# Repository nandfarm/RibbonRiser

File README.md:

# RibbonRiser
Lenovo Tiny 5 series riser card with a ribbon extension to connect an extra NVME and preserve an x16 PCIe connector

"This project is sponsored by PCBWay. Whether for small projects or complex designs, PCBWay offers quality PCB manufacturing, PCBA services, and CNC machining with industry-leading customization options, competitive pricing, and high-quality, end-to-end service. Prototype PCB orders start at a minimum of 5 pieces, with prices as low as $5. Learn more at www.pcbway.com ."

This is a prototype version of the device intended to check the impedance traces and the ribbon design. DO NOT reproduce as it is not guaranteed to work yet.

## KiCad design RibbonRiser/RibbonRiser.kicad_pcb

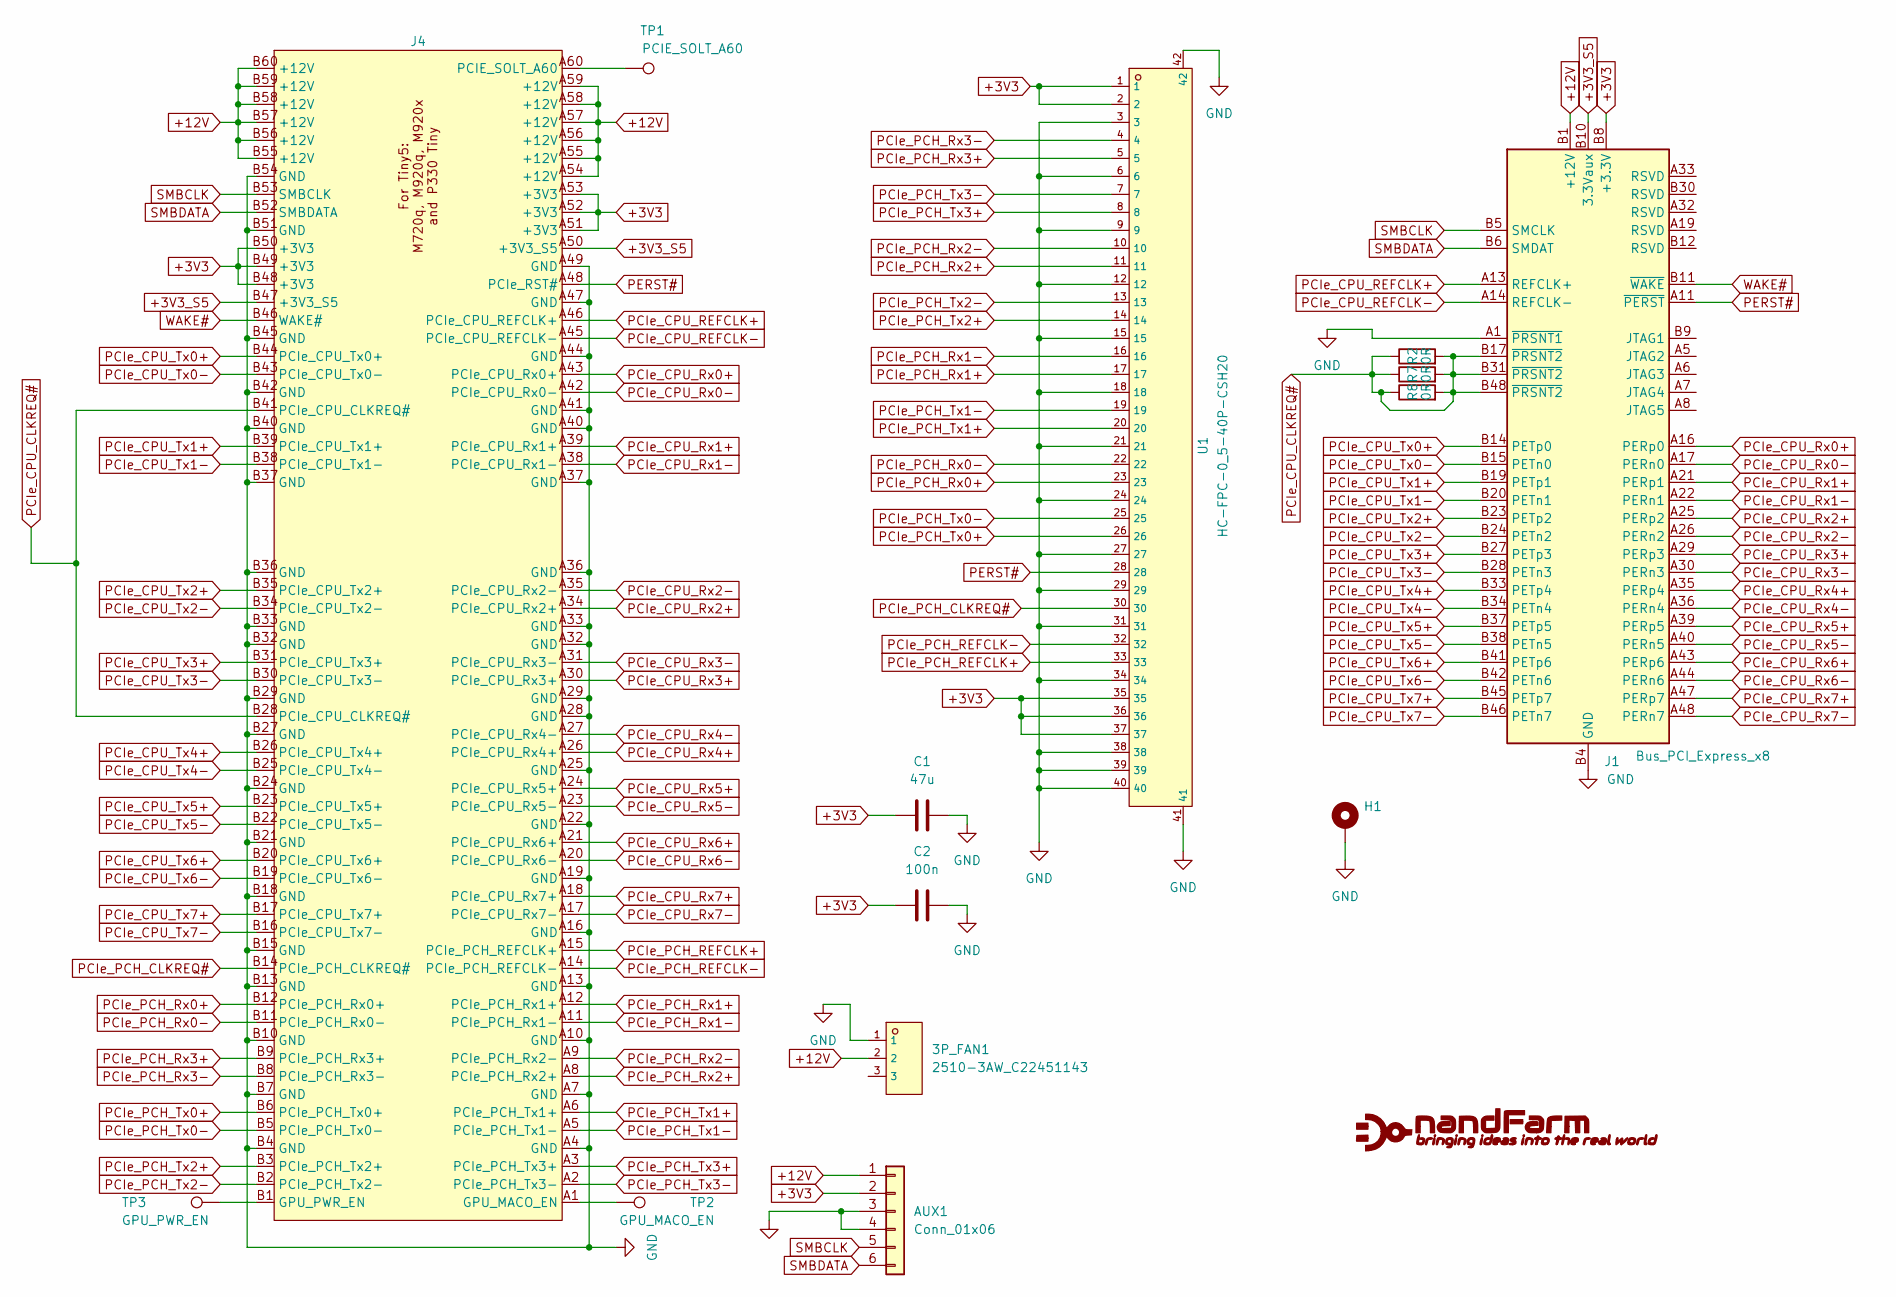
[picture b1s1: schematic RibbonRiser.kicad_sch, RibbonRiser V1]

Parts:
3P_FAN1: 2510-3AW_C22451143; CONN-TH_2510-3AW; LCSC C22451143
AUX1: Conn_01x06; PinHeader_1x06_P2.54mm_Vertical
C1: 47u; C_1206_3216Metric_Pad1.33x1.80mm_HandSolder
C2: 100n; C_0805_2012Metric_Pad1.18x1.45mm_HandSolder
H1: MountingHole_Pad; MountingHole_4.3mm_M4_ISO7380_Pad_TopOnly
J1: Bus_PCI_Express_x8; CONN-TH_98P-P1.00-V_3183-XXXXXPXT
J4: TinyRiser_connector
R2, R7, R8: 0R; R_0603_1608Metric_Pad0.98x0.95mm_HandSolder
TP1: PCIE_SOLT_A60; TestPoint_Pad_D1.0mm
TP2: GPU_MACO_EN; TestPoint_Pad_D1.0mm
TP3: GPU_PWR_EN; TestPoint_Pad_D1.0mm
U1: HC-FPC-0_5-40P-CSH20; FPC-SMD_40P-P0.50_HC-FPC-0.5-40P-CSH20; LCSC C19273956

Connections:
+3V3: AUX1.2, C1.1, C2.1, J1.A9 (+3.3V), J1.A10 (+3.3V), J1.B8 (+3.3V), J4.A51 (+3V3), J4.A52 (+3V3), J4.A53 (+3V3), J4.B48 (+3V3), J4.B49 (+3V3), J4.B50 (+3V3), U1.1, U1.2, U1.35, U1.36, U1.37
+3V3_S5: J1.B10 (3.3Vaux), J4.A50 (+3V3_S5), J4.B47 (+3V3_S5)
+12V: 3P_FAN1.2, AUX1.1, J1.A2 (+12V), J1.A3 (+12V), J1.B1 (+12V), J1.B2 (+12V), J1.B3 (+12V), J4.A54 (+12V), J4.A55 (+12V), J4.A56 (+12V), J4.A57 (+12V), J4.A58 (+12V), J4.A59 (+12V), J4.B55 (+12V), J4.B56 (+12V), J4.B57 (+12V), J4.B58 (+12V), J4.B59 (+12V), J4.B60 (+12V)
GND: 3P_FAN1.1, AUX1.3, AUX1.4, C1.2, C2.2, H1.1, J1.A1 (~PRSNT1), J1.A4 (GND), J1.A12 (GND), J1.A15 (GND), J1.A18 (GND), J1.A20 (GND), J1.A23 (GND), J1.A24 (GND), J1.A27 (GND), J1.A28 (GND), J1.A31 (GND), J1.A34 (GND), J1.A37 (GND), J1.A38 (GND), J1.A41 (GND), J1.A42 (GND), J1.A45 (GND), J1.A46 (GND), J1.A49 (GND), J1.B4 (GND), J1.B7 (GND), J1.B13 (GND), J1.B16 (GND), J1.B18 (GND), J1.B21 (GND), J1.B22 (GND), J1.B25 (GND), J1.B26 (GND), J1.B29 (GND), J1.B32 (GND), J1.B35 (GND), J1.B36 (GND), J1.B39 (GND), J1.B40 (GND), J1.B43 (GND), J1.B44 (GND), J1.B47 (GND), J1.B49 (GND), J4.A4 (GND), J4.A7 (GND), J4.A10 (GND), J4.A13 (GND), J4.A16 (GND), J4.A19 (GND), J4.A22 (GND), J4.A25 (GND), J4.A28 (GND), J4.A29 (GND), J4.A32 (GND), J4.A33 (GND), J4.A36 (GND), J4.A37 (GND), J4.A40 (GND), J4.A41 (GND), J4.A44 (GND), J4.A47 (GND), J4.A49 (GND), J4.B4 (GND), J4.B7 (GND), J4.B10 (GND), J4.B13 (GND), J4.B15 (GND), J4.B18 (GND), J4.B21 (GND), J4.B24 (GND), J4.B27 (GND), J4.B29 (GND), J4.B32 (GND), J4.B33 (GND), J4.B36 (GND), J4.B37 (GND), J4.B40 (GND), J4.B42 (GND), J4.B45 (GND), J4.B51 (GND), J4.B54 (GND), U1.3, U1.6, U1.9, U1.12, U1.15, U1.18, U1.21, U1.24, U1.27, U1.29, U1.31, U1.34, U1.38, U1.39, U1.40, U1.41, U1.42
unnamed: J4.A1 (GPU_MACO_EN), TP2.1
unnamed: J4.B1 (GPU_PWR_EN), TP3.1
unnamed: J4.A60 (PCIE_SOLT_A60), TP1.1
PCIe_CPU_CLKREQ#: J1.B17 (~PRSNT2), J1.B31 (~PRSNT2), J1.B48 (~PRSNT2), J4.B28 (PCIe_CPU_CLKREQ#), J4.B41 (PCIe_CPU_CLKREQ#), R2.1, R2.2, R7.1, R7.2, R8.1, R8.2
PCIe_CPU_REFCLK+: J1.A13 (REFCLK+), J4.A46 (PCIe_CPU_REFCLK+)
PCIe_CPU_REFCLK-: J1.A14 (REFCLK-), J4.A45 (PCIe_CPU_REFCLK-)
PCIe_CPU_Rx0+: J1.A16 (PERp0), J4.A43 (PCIe_CPU_Rx0+)
PCIe_CPU_Rx0-: J1.A17 (PERn0), J4.A42 (PCIe_CPU_Rx0-)
PCIe_CPU_Rx1+: J1.A21 (PERp1), J4.A39 (PCIe_CPU_Rx1+)
PCIe_CPU_Rx1-: J1.A22 (PERn1), J4.A38 (PCIe_CPU_Rx1-)
PCIe_CPU_Rx2+: J1.A25 (PERp2), J4.A34 (PCIe_CPU_Rx2+)
PCIe_CPU_Rx2-: J1.A26 (PERn2), J4.A35 (PCIe_CPU_Rx2-)
PCIe_CPU_Rx3+: J1.A29 (PERp3), J4.A30 (PCIe_CPU_Rx3+)
PCIe_CPU_Rx3-: J1.A30 (PERn3), J4.A31 (PCIe_CPU_Rx3-)
PCIe_CPU_Rx4+: J1.A35 (PERp4), J4.A26 (PCIe_CPU_Rx4+)
PCIe_CPU_Rx4-: J1.A36 (PERn4), J4.A27 (PCIe_CPU_Rx4-)
PCIe_CPU_Rx5+: J1.A39 (PERp5), J4.A24 (PCIe_CPU_Rx5+)
PCIe_CPU_Rx5-: J1.A40 (PERn5), J4.A23 (PCIe_CPU_Rx5-)
PCIe_CPU_Rx6+: J1.A43 (PERp6), J4.A21 (PCIe_CPU_Rx6+)
PCIe_CPU_Rx6-: J1.A44 (PERn6), J4.A20 (PCIe_CPU_Rx6-)
PCIe_CPU_Rx7+: J1.A47 (PERp7), J4.A18 (PCIe_CPU_Rx7+)
PCIe_CPU_Rx7-: J1.A48 (PERn7), J4.A17 (PCIe_CPU_Rx7-)
PCIe_CPU_Tx0+: J1.B14 (PETp0), J4.B44 (PCIe_CPU_Tx0+)
PCIe_CPU_Tx0-: J1.B15 (PETn0), J4.B43 (PCIe_CPU_Tx0-)
PCIe_CPU_Tx1+: J1.B19 (PETp1), J4.B39 (PCIe_CPU_Tx1+)
PCIe_CPU_Tx1-: J1.B20 (PETn1), J4.B38 (PCIe_CPU_Tx1-)
PCIe_CPU_Tx2+: J1.B23 (PETp2), J4.B35 (PCIe_CPU_Tx2+)
PCIe_CPU_Tx2-: J1.B24 (PETn2), J4.B34 (PCIe_CPU_Tx2-)
PCIe_CPU_Tx3+: J1.B27 (PETp3), J4.B31 (PCIe_CPU_Tx3+)
PCIe_CPU_Tx3-: J1.B28 (PETn3), J4.B30 (PCIe_CPU_Tx3-)
PCIe_CPU_Tx4+: J1.B33 (PETp4), J4.B26 (PCIe_CPU_Tx4+)
PCIe_CPU_Tx4-: J1.B34 (PETn4), J4.B25 (PCIe_CPU_Tx4-)
PCIe_CPU_Tx5+: J1.B37 (PETp5), J4.B23 (PCIe_CPU_Tx5+)
PCIe_CPU_Tx5-: J1.B38 (PETn5), J4.B22 (PCIe_CPU_Tx5-)
PCIe_CPU_Tx6+: J1.B41 (PETp6), J4.B20 (PCIe_CPU_Tx6+)
PCIe_CPU_Tx6-: J1.B42 (PETn6), J4.B19 (PCIe_CPU_Tx6-)
PCIe_CPU_Tx7+: J1.B45 (PETp7), J4.B17 (PCIe_CPU_Tx7+)
PCIe_CPU_Tx7-: J1.B46 (PETn7), J4.B16 (PCIe_CPU_Tx7-)
PCIe_PCH_CLKREQ#: J4.B14 (PCIe_PCH_CLKREQ#), U1.30
PCIe_PCH_REFCLK+: J4.A15 (PCIe_PCH_REFCLK+), U1.33
PCIe_PCH_REFCLK-: J4.A14 (PCIe_PCH_REFCLK-), U1.32
PCIe_PCH_Rx0+: J4.B12 (PCIe_PCH_Rx0+), U1.23
PCIe_PCH_Rx0-: J4.B11 (PCIe_PCH_Rx0-), U1.22
PCIe_PCH_Rx1+: J4.A12 (PCIe_PCH_Rx1+), U1.17
PCIe_PCH_Rx1-: J4.A11 (PCIe_PCH_Rx1-), U1.16
PCIe_PCH_Rx2+: J4.A8 (PCIe_PCH_Rx2+), U1.11
PCIe_PCH_Rx2-: J4.A9 (PCIe_PCH_Rx2-), U1.10
PCIe_PCH_Rx3+: J4.B9 (PCIe_PCH_Rx3+), U1.5
PCIe_PCH_Rx3-: J4.B8 (PCIe_PCH_Rx3-), U1.4
PCIe_PCH_Tx0+: J4.B6 (PCIe_PCH_Tx0+), U1.26
PCIe_PCH_Tx0-: J4.B5 (PCIe_PCH_Tx0-), U1.25
PCIe_PCH_Tx1+: J4.A6 (PCIe_PCH_Tx1+), U1.20
PCIe_PCH_Tx1-: J4.A5 (PCIe_PCH_Tx1-), U1.19
PCIe_PCH_Tx2+: J4.B3 (PCIe_PCH_Tx2+), U1.14
PCIe_PCH_Tx2-: J4.B2 (PCIe_PCH_Tx2-), U1.13
PCIe_PCH_Tx3+: J4.A3 (PCIe_PCH_Tx3+), U1.8
PCIe_PCH_Tx3-: J4.A2 (PCIe_PCH_Tx3-), U1.7
PERST#: J1.A11 (~PERST), J4.A48 (PCIe_RST#), U1.28
SMBCLK: AUX1.5, J1.B5 (SMCLK), J4.B53 (SMBCLK)
SMBDATA: AUX1.6, J1.B6 (SMDAT), J4.B52 (SMBDATA)
WAKE#: J1.B11 (~WAKE), J4.B46 (WAKE#)

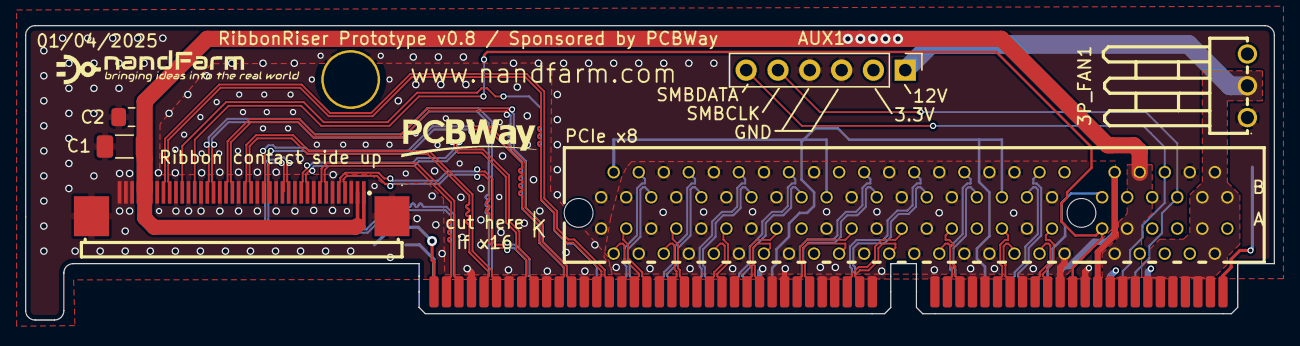
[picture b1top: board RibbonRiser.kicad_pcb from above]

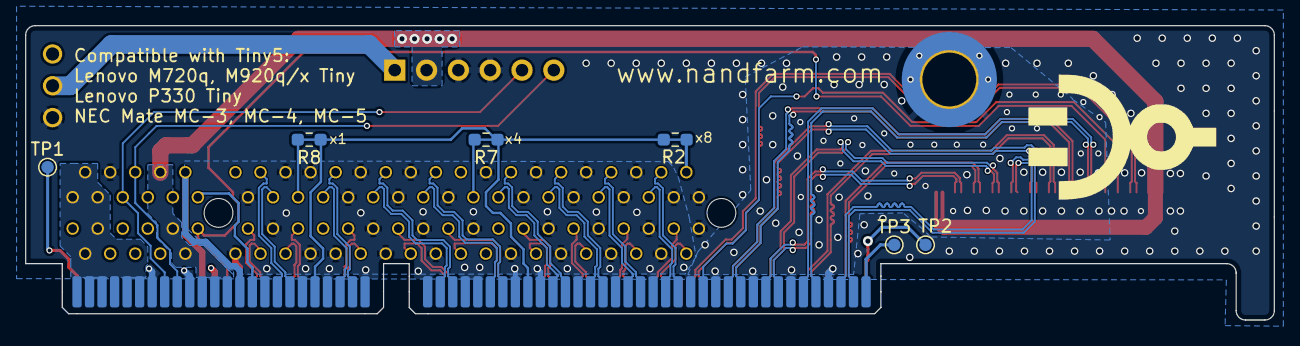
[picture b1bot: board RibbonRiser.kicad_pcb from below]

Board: 4 copper layers, 99.7 x 23.5 mm, 14 parts (8 on the bottom side), 65 nets.

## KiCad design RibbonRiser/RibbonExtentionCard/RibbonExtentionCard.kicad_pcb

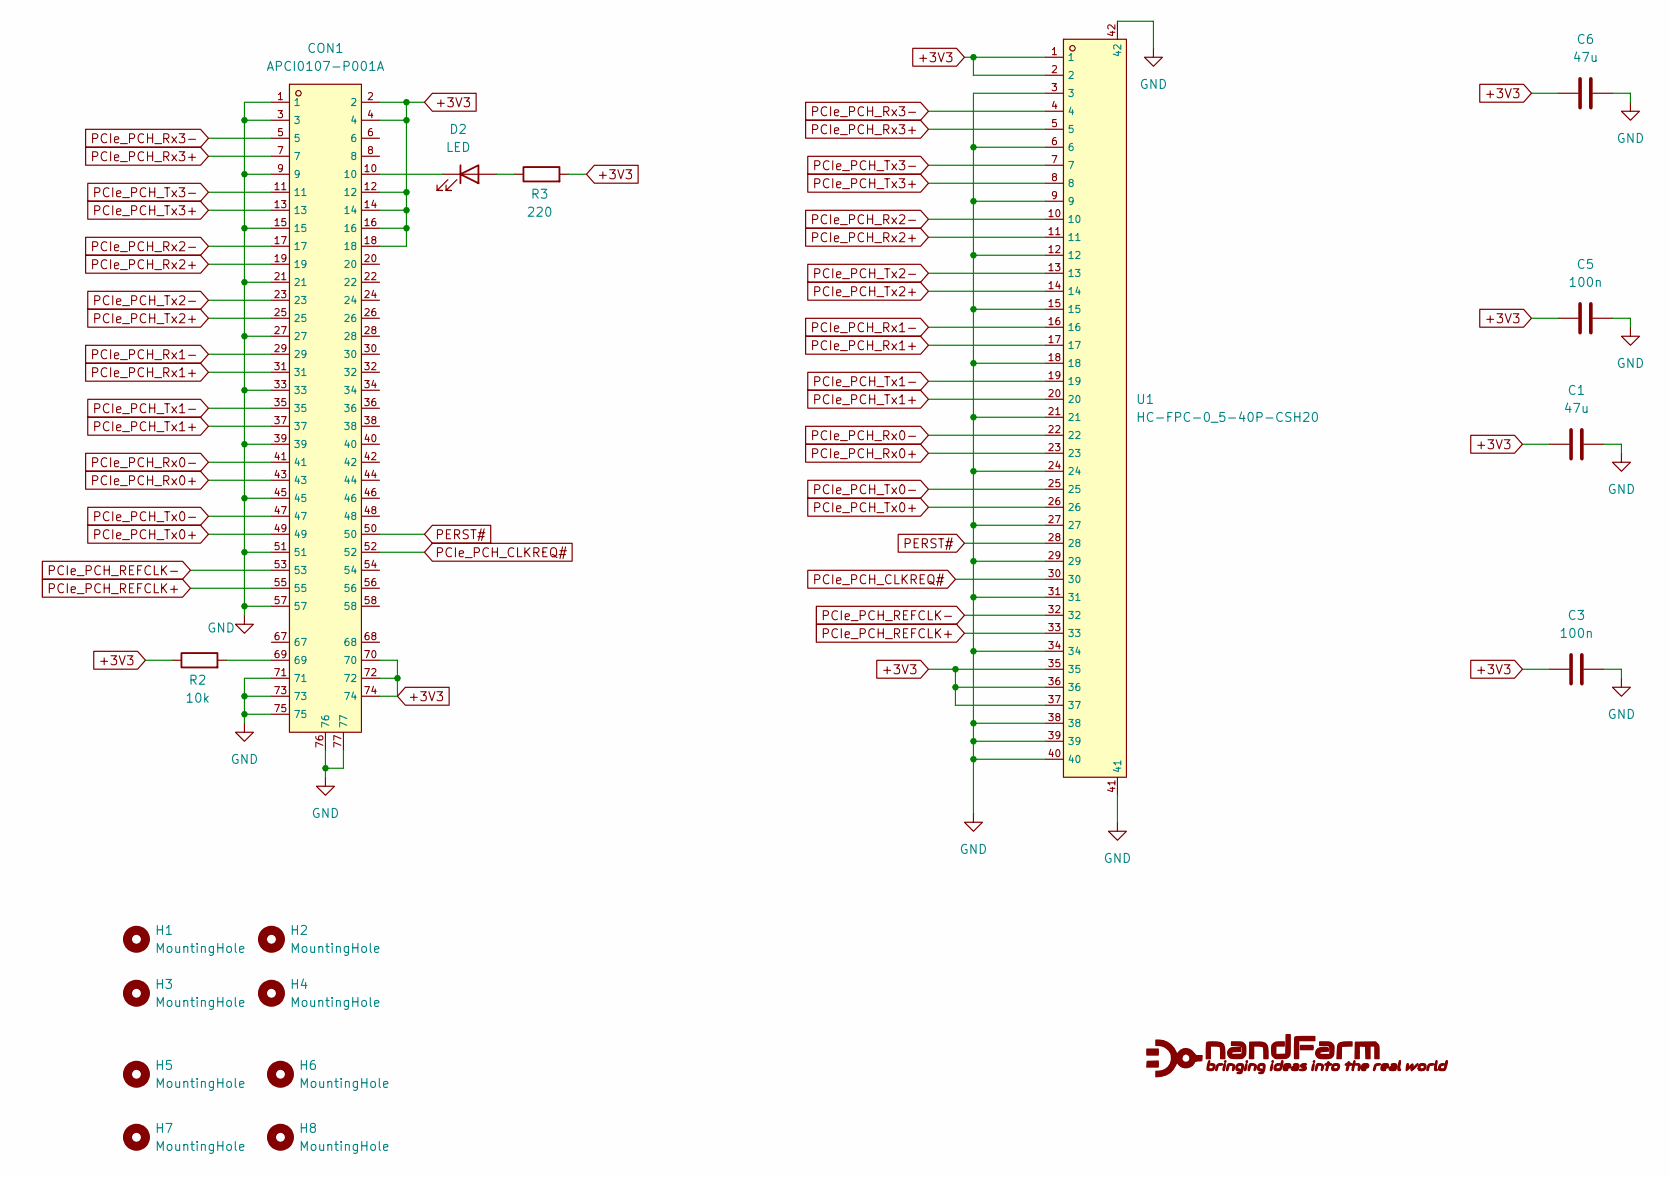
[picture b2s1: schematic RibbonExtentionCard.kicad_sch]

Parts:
C1, C6: 47u; C_1206_3216Metric_Pad1.33x1.80mm_HandSolder
C3, C5: 100n; C_0805_2012Metric_Pad1.18x1.45mm_HandSolder
CON1: APCI0107-P001A; CONN-SMD_APCI0107-P001A; LCSC C841661
D2: LED; LED_0805_2012Metric
H1, H2, H3, H4, H5, H6, H7, H8: MountingHole; MountingHole_3.2mm_M3
R2: 10k; R_0805_2012Metric_Pad1.20x1.40mm_HandSolder
R3: 220; R_0805_2012Metric_Pad1.20x1.40mm_HandSolder
U1: HC-FPC-0_5-40P-CSH20; FPC-SMD_40P-P0.50_HC-FPC-0.5-40P-CSH20; LCSC C19273956

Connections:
+3V3: C1.1, C3.1, C5.1, C6.1, CON1.2, CON1.4, CON1.12, CON1.14, CON1.16, CON1.18, CON1.70, CON1.72, CON1.74, R2.1, R3.2, U1.1, U1.2, U1.35, U1.36, U1.37
GND: C1.2, C3.2, C5.2, C6.2, CON1.1, CON1.3, CON1.9, CON1.15, CON1.21, CON1.27, CON1.33, CON1.39, CON1.45, CON1.51, CON1.57, CON1.71, CON1.73, CON1.75, CON1.76, CON1.77, U1.3, U1.6, U1.9, U1.12, U1.15, U1.18, U1.21, U1.24, U1.27, U1.29, U1.31, U1.34, U1.38, U1.39, U1.40, U1.41, U1.42
unnamed: CON1.69, R2.2
unnamed: D2.2 (A), R3.1
unnamed: CON1.10, D2.1 (K)
PCIe_PCH_CLKREQ#: CON1.52, U1.30
PCIe_PCH_REFCLK+: CON1.55, U1.33
PCIe_PCH_REFCLK-: CON1.53, U1.32
PCIe_PCH_Rx0+: CON1.43, U1.23
PCIe_PCH_Rx0-: CON1.41, U1.22
PCIe_PCH_Rx1+: CON1.31, U1.17
PCIe_PCH_Rx1-: CON1.29, U1.16
PCIe_PCH_Rx2+: CON1.19, U1.11
PCIe_PCH_Rx2-: CON1.17, U1.10
PCIe_PCH_Rx3+: CON1.7, U1.5
PCIe_PCH_Rx3-: CON1.5, U1.4
PCIe_PCH_Tx0+: CON1.49, U1.26
PCIe_PCH_Tx0-: CON1.47, U1.25
PCIe_PCH_Tx1+: CON1.37, U1.20
PCIe_PCH_Tx1-: CON1.35, U1.19
PCIe_PCH_Tx2+: CON1.25, U1.14
PCIe_PCH_Tx2-: CON1.23, U1.13
PCIe_PCH_Tx3+: CON1.13, U1.8
PCIe_PCH_Tx3-: CON1.11, U1.7
PERST#: CON1.50, U1.28

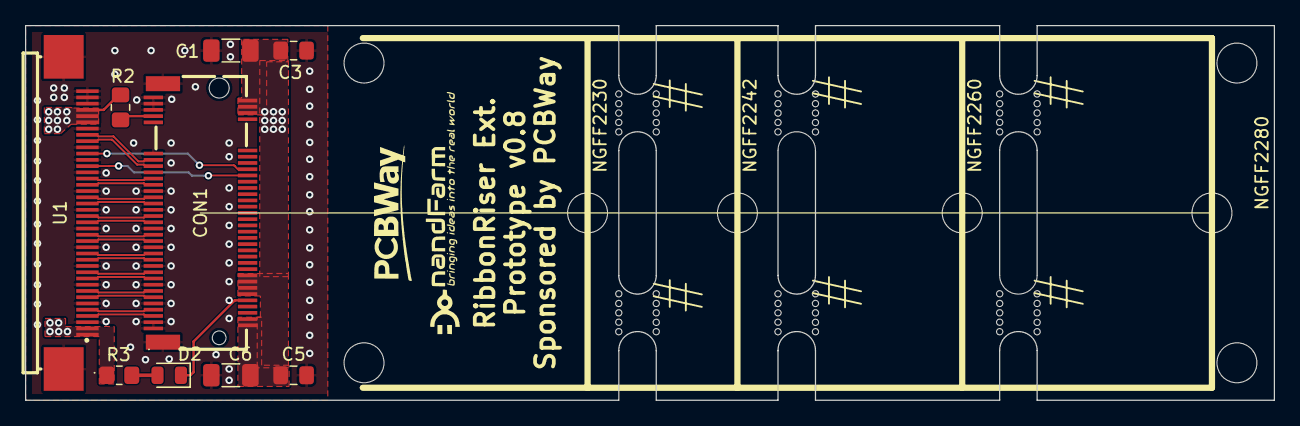
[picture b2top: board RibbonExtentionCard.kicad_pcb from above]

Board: 4 copper layers, 100.0 x 30.0 mm, 23 parts (0 on the bottom side), 25 nets.

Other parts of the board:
mouse-bite-3mm-slot, mouse-bite-3mm-slot#2, mouse-bite-3mm-slot#3, mouse-bite-3mm-slot#4, mouse-bite-3mm-slot#5, mouse-bite-3mm-slot#6: VAL**; mouse-bite-3mm-slot

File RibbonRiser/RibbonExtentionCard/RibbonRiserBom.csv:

"Reference","Value","Datasheet","Footprint","Qty","DNP"
"C1,C6","47u","~","Capacitor_SMD:C_1206_3216Metric_Pad1.33x1.80mm_HandSolder","2",""
"C3,C5","100n","~","Capacitor_SMD:C_0805_2012Metric_Pad1.18x1.45mm_HandSolder","2",""
"CON1","APCI0107-P001A","https://item.szlcsc.com/899447.html","importedlibs:CONN-SMD_APCI0107-P001A","1",""
"D2","LED","~","LED_SMD:LED_0805_2012Metric","1",""
"R2","10k","~","Resistor_SMD:R_0805_2012Metric_Pad1.20x1.40mm_HandSolder","1",""
"R3","220","~","Resistor_SMD:R_0805_2012Metric_Pad1.20x1.40mm_HandSolder","1",""
"U1","HC-FPC-0_5-40P-CSH20","https://atta.szlcsc.com/upload/public/pdf/source/20231201/8F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","importedlibs:FPC-SMD_40P-P0.50_HC-FPC-0.5-40P-CSH20","1",""
